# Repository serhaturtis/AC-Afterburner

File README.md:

<div id="top"></div>

<br />
<div align="center">

<h3 align="center">AFTERBURNER</h3>

  <p align="center">
    An Ibanez TS-9 Clone Board 
  </p>
</div>

<!-- WHAT -->
## What?

This is an overdrive guitar effects board, "inspired" by the Ibanez Tube Screamer 9.

## Why?

I wanted to test the effects so that I can use them on another project. So I made standalone clone boards. This is one of them.

## How?

This is imported from Eagle to KiCad 6 while I was backing up my projects. So the schematic's look is a bit janky.

Diodes are used for clipping, can experiment with different combinations, LEDs etc.

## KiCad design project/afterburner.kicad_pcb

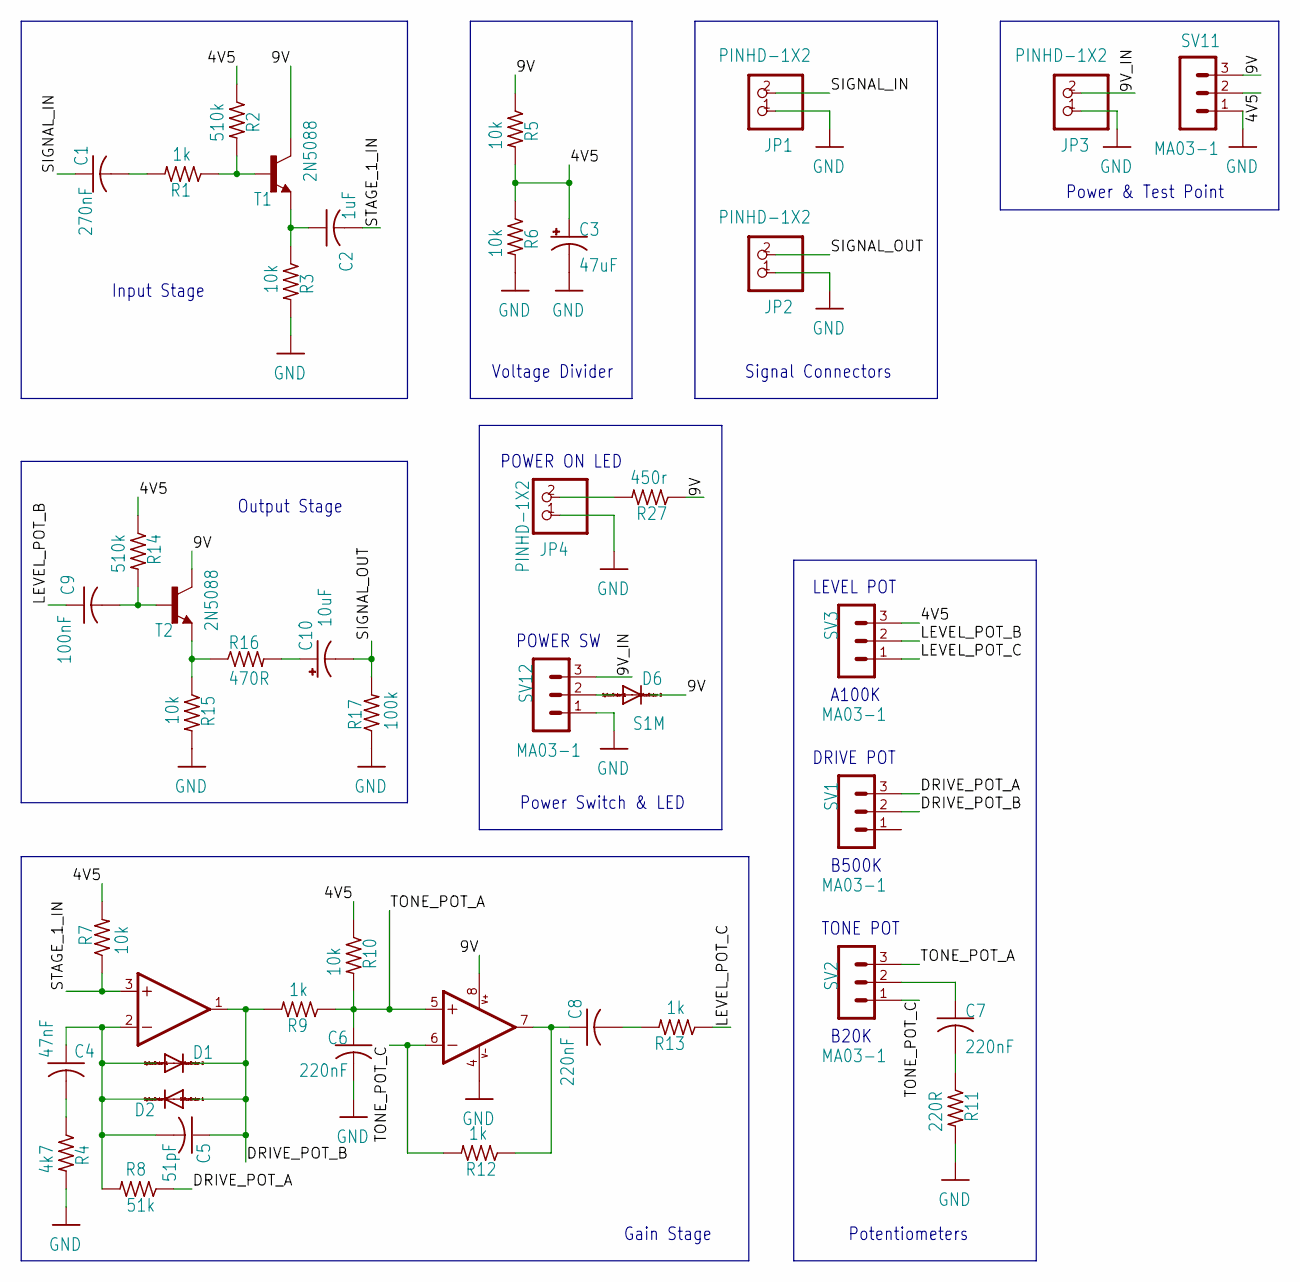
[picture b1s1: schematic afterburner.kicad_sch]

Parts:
C1: 270nF; C0805
C2: 1uF; C0805
C3: 47uF; UD-6,3X5,8_NICHICON
C4: 47nF; C0805
C5: 51pF; C0805
C6, C7, C8: 220nF; C0805
C9: 100nF; C0805
C10: 10uF; UD-4X5,8_NICHICON
D1, D2: 1N4148DO35-7; DO35-7
D6: S1M; SMA
IC1: TL072P; DIL08
JP1, JP2, JP3, JP4: PINHD-1X2; 1X02
R1, R9, R12, R13: 1k; R0805
R2, R14: 510k; R0805
R3, R5, R6, R7, R10, R15: 10k; R0805
R4: 4k7; R0805
R8: 51k; R0805
R11: 220R; R0805
R16: 470R; R0805
R17: 100k; R0805
R27: 450r; R0805
SV1, SV2, SV3, SV11, SV12: MA03-1
T1, T2: 2N5088; TO92

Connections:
4V5: C3.+, R2.1, R5.2, R6.1, R7.2, R10.1, R14.1, SV3.3, SV11.2
9V: D6.C, IC1.8 (V+), R5.1, R27.1, SV11.3, T1.1 (C), T2.1 (C)
9V_IN: JP3.2, SV12.3
DRIVE_POT_A: R8.1, SV1.3
DRIVE_POT_B: C5.1, D1.C, D2.A, IC1.1 (OUT), R9.2, SV1.2
GND: C3.-, C6.2, IC1.4 (V-), JP1.1, JP2.1, JP3.1, JP4.1, R3.2, R4.2, R6.2, R11.2, R15.2, R17.1, SV11.1, SV12.1
LEVEL_POT_B: C9.1, SV3.2
LEVEL_POT_C: R13.1, SV3.1
unnamed: C1.2, R1.2
unnamed: R1.1, R2.2, T1.2 (B)
unnamed: C2.1, R3.1, T1.3 (E)
unnamed: C8.2, R13.2
unnamed: C4.1, C5.2, D1.A, D2.C, IC1.2 (-IN), R8.2
unnamed: C7.1, SV2.2
unnamed: C8.1, IC1.7 (OUT), R12.1
unnamed: C4.2, R4.1
unnamed: C7.2, R11.1
unnamed: C9.2, R14.2, T2.2 (B)
unnamed: D6.A, SV12.2
unnamed: JP4.2, R27.2
unnamed: R15.1, R16.1, T2.3 (E)
unnamed: C10.+, R16.2
SIGNAL_IN: C1.1, JP1.2
SIGNAL_OUT: C10.-, JP2.2, R17.2
STAGE_1_IN: C2.2, IC1.3 (+IN), R7.1
TONE_POT_A: C6.1, IC1.5 (+IN), R9.1, R10.2, SV2.3
TONE_POT_C: IC1.6 (-IN), R12.2, SV2.1

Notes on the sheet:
Signal Connectors
Input Stage
DRIVE POT
LEVEL POT
POWER ON LED
Potentiometers
Gain Stage
B20K
Output Stage
Power & Test Point
B500K
Power Switch & LED
Voltage Divider
A100K
TONE POT
POWER SW

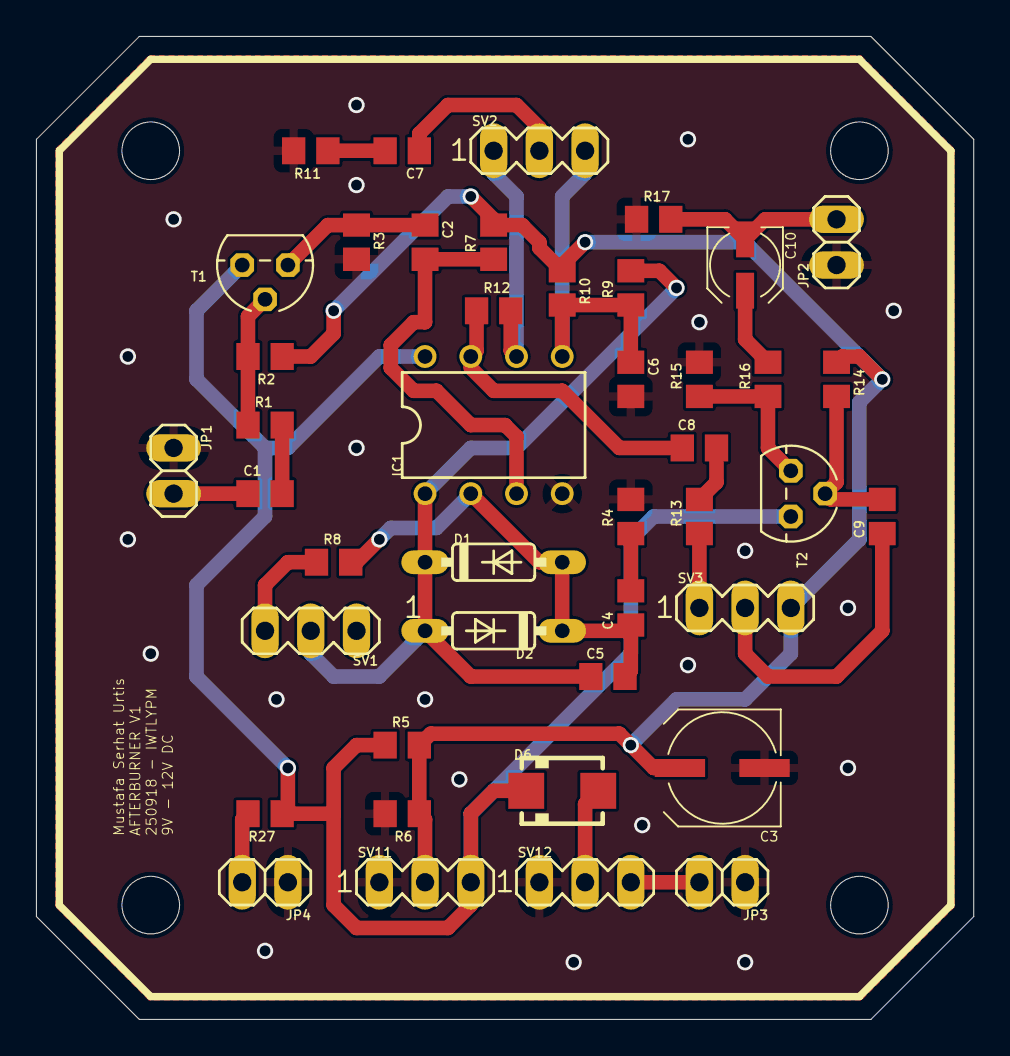
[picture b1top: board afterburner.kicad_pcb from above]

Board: 2 copper layers, 52.1 x 54.6 mm, 47 parts (0 on the bottom side), 27 nets.

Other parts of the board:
@HOLE0, @HOLE1, @HOLE2, @HOLE3: (no value)

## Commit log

2022-01-12 fixed image
2022-01-12 fixed images
